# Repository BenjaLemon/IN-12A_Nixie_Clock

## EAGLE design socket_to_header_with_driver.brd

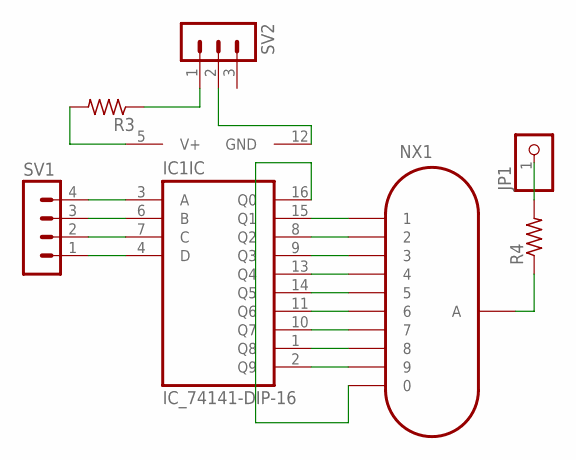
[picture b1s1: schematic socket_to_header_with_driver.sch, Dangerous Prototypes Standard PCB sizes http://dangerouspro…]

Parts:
IC1: IC_74141-DIP-16; DIL16
JP1: PINHD-1X1; 1X01
NX1: IN-12A; IN-12
R3, R4: R-US_0204/7; 0204/7
SV1: MA04-1
SV2: MA03-1

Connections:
GND: IC1.12 (GND), SV2.2
unnamed: IC1.2 (Q9), NX1.9
unnamed: IC1.1 (Q8), NX1.8
unnamed: IC1.10 (Q7), NX1.7
unnamed: IC1.11 (Q6), NX1.6
unnamed: IC1.14 (Q5), NX1.5
unnamed: IC1.13 (Q4), NX1.4
unnamed: IC1.9 (Q3), NX1.3
unnamed: IC1.8 (Q2), NX1.2
unnamed: IC1.15 (Q1), NX1.1
unnamed: IC1.16 (Q0), NX1.0
unnamed: NX1.A, R4.1
unnamed: JP1.1, R4.2
unnamed: IC1.4 (D), SV1.1
unnamed: IC1.7 (C), SV1.2
unnamed: IC1.6 (B), SV1.3
unnamed: IC1.3 (A), SV1.4
unnamed: R3.1, SV2.1
V+: IC1.5 (V+), R3.2

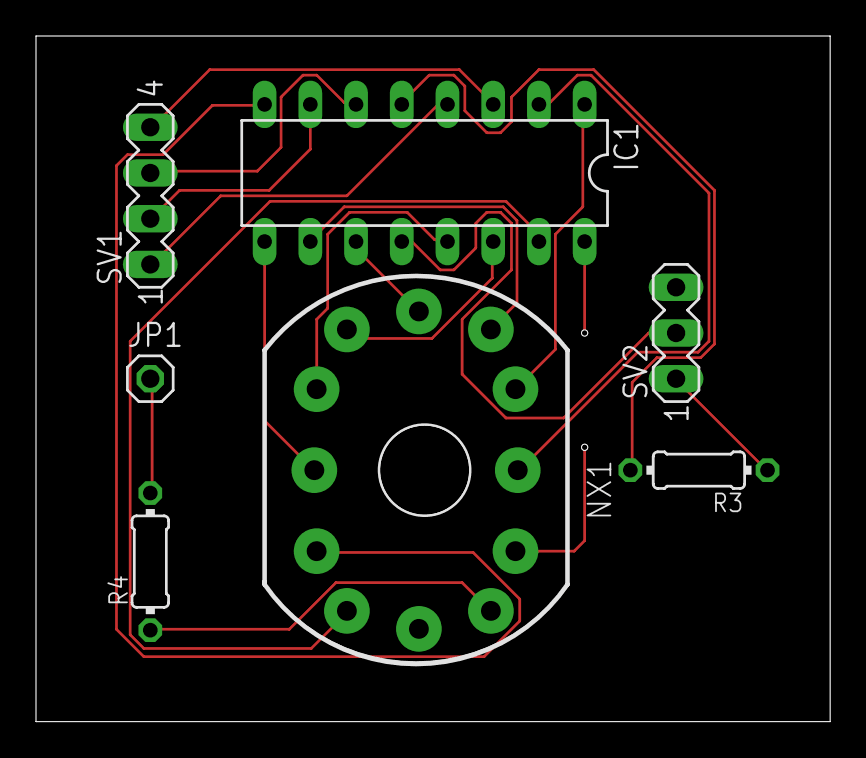
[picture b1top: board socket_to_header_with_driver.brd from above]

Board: 2 copper layers, 44.1 x 38.1 mm, 7 parts (0 on the bottom side), 19 nets.
